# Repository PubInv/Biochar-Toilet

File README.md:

# Current Status

Phase 1 (conductive heating prototype) is complete. All experiment data, firmware, schematics, PCB design files, and progress reports are in the [`Conductive Heating Prototype/`](https://github.com/PubInv/Biochar-Toilet/tree/main/Project%20Files/Conductive%20Heating%20Prototype) folder.

We're now in Phase 2: induction heating using a magnetite matrix. The shift from resistive heating matters because induction generates heat directly inside the charring cup — no exposed coils corroding in the process environment, and faster energy delivery to the material itself.

Ongoing experiment logs are in the [Progress Reports](https://github.com/PubInv/Biochar-Toilet/blob/main/Project%20Files/Progress%20Reports.md).

---

# Biochar Toilet

A reliable toilet that could quickly reduce human fecal matter to completely sanitary biochar would make the poorest people of the
Earth healthier. In many communities, Western-style sewage systems would be very expensive and impractical due to
geology, the lack of density in farming communities made of small land holdings, a lack of capital, and a lack of
social and political organization to dig trenches and lay pipes efficiently.

Reducing a typical human stool to biochar requires an energy input of about 600 kilojoules (see detailed analysis in referenced spreadsheet).
Even for the poorest people, the cost of this electricity is quite low---less than one US cent $0.01USD. One kilowatt hour is 3.6 MJ (megajoules).
Expensive electrical power around the world is $0.45/kWh is $0.075 USD--or less than eight cents. Even if our toilet is inefficient, it
seems possible to make a toilet whose operating cost is affordable for the poorest people, at $27.375 per year (this cost does not include
the capital costs of the toilet).

Biochar can be used as a fuel or a garden amendment. Note, however, that human stools are so small (128 grams nominally) that this is not a meaningful approach for carbon sequestration.

# Initial Design Idea

The problem of toilets is a widely researched area. Our approach may be slightly novel. We start from some assumptions:

1. Electricity is an input.
2. Complete biological safety of the end product is required.
3. We choose to temporarily ignore the capital costs of the toilet in our research.
4. Because we have to char in the absence of oxygen to prevent combustion, we can assume that we need an air-tight or pressure controlled reaction vessel.
5. A major problem in charring is to first dry the sample, and drying is primarily a problem of water transport.

We therefore conclude that our basic design will be a sealed reaction vessel with a valve that allows steam to be transported out
of the reaction chamber. We will heat the chamber contents until a desired pressure is created and then transport the water
vapor away by opening the valve. The valve will be controlled so as to avoid most gases (air) from entering the chamber.
Opening the valve will "flash" the water in the sample into steam, which will have the desirable properties of being
extremely murderous to any organisms present in the sample, and physically destructive to both plant and animal cells.
It may even physically disrupt the sample, which could be advantageous.

When the sample is sufficiently dry, we will heat it to charring temperature. When the sample is fully charred, and then cooled
and possibly wetted to avoid spontaneous combustion, the operator will be alerted that the sample is safe to remove and either combust or use as a garden amendment.

# Energy Analysis

Volunteer Nupur Bhalla working with Invention Coach Robert L. Read has produced a [Google Sheet](https://docs.google.com/spreadsheets/d/1ZwIqP0B2wM6QrpZTNiK1hNnNmIEIal7qxYdgEJz8Iog/edit?usp=sharing) representing an energy analysis of the drying and heating process.

# Heating Mechanisms

Since we will have a sealed metal reaction vessel, radio frequency (RF) heating is a possibility.
However, it is expected to become less effective as the sample dries.
We therefore intend to explore the possibility of using simple Joule resistive heating of a stainless steel vessel directly.
RF heating, however, has the advantage of heating the sample volumetrically (not requiring conduction), which may be a tremendous advantage.

# Phase 1: Conductive Heating Prototype (Complete)

Phase 1 used a pressure cooker as the reaction vessel, a hot plate controlled by an SSR, and an ESP32-based sensing system. The goal was to confirm the core architecture before committing to higher-temperature methods.

It worked. When pressure drops below ~1 PSI while temperature keeps climbing, the system correctly identifies the dry state and cuts heater power automatically. Flash decompression also checked out — opening the solenoid under pressure causes trapped water to flash to steam. A bread charring test (~110°C, 2h40m) produced a visibly charred loaf, though the dryness algorithm didn't trigger since the bread's low moisture content didn't produce a distinct enough pressure signature during drying. Soot accumulation on the lid also flagged particulate management as something to design for in future iterations.

The hard limit we hit: full charring temperatures aren't safe inside a standard pressure cooker. Lawrence Kincheloe suggested placing an inner cup (heated by a silicon nitride igniter) inside the vessel so the outer shell stays cool — that idea feeds directly into Phase 2.

We also designed a custom control PCB for this phase (ESP32-H2, v0.3.0) with dual MOSFET valve drivers, dual SSR outputs, a pressure ADC, and a MAX31855 thermocouple interface. Everything is in the [`Conductive Heating Prototype/`](https://github.com/PubInv/Biochar-Toilet/tree/main/Project%20Files/Conductive%20Heating%20Prototype) folder.

# Phase 2: Induction System Development (In Progress)

We've switched from resistive heating to pulsed induction using a magnetite matrix. The magnetite sits inside the charring cup and converts the induction field directly into heat — no exposed coils, no conduction losses through the vessel wall.

Early results from Lawrence Kincheloe and Peter are encouraging. Five grams of magnetite reached 740°F in 60 seconds; the same mass of carbon steel bearings only hit 130°F. Volume-matching the steel to the magnetite closes the gap considerably (~940°F peak), which suggests surface area and density matter more than material choice at this scale. They also charred cheese puffs at 833°F over 16 minutes in open air, with residue on the crucible cap showing evidence of partial pyrolysis.

Full experiment logs are in the [Progress Reports](https://github.com/PubInv/Biochar-Toilet/blob/main/Project%20Files/Progress%20Reports.md).

# Research Plans

The next step is pushing the induction system to actual charring temperatures — hot enough to produce biochar from organic material comparable to human stool. Work on coil geometry and magnetic field focusing is ongoing in parallel with fabrication.

# References

"An Experimental 13.56 MHz Radio Frequency Heating System
for Efficient Thermal Pretreatment of Wastewater Sludge",
Md. S. Ferdous, Ehssan H. Koupaie, Cigdem Eskicioglu, and Thomas Johnson*

# Volunteer Opportunities

This project is still active. If you have a background in mechanical engineering, heat engineering, or chemistry, we'd be glad to hear from you.

Reach out to Inventor Coach [Robert L. Read](https://github.com/PubInv/Biochar-Toilet/blob/main/read.robert@gmail.com) or Volunteer Coordinator [Miriam Castillo](https://www.linkedin.com/in/cstllgtrrz/). More at the [Volunteer Page](https://www.pubinv.org/volunteer/).

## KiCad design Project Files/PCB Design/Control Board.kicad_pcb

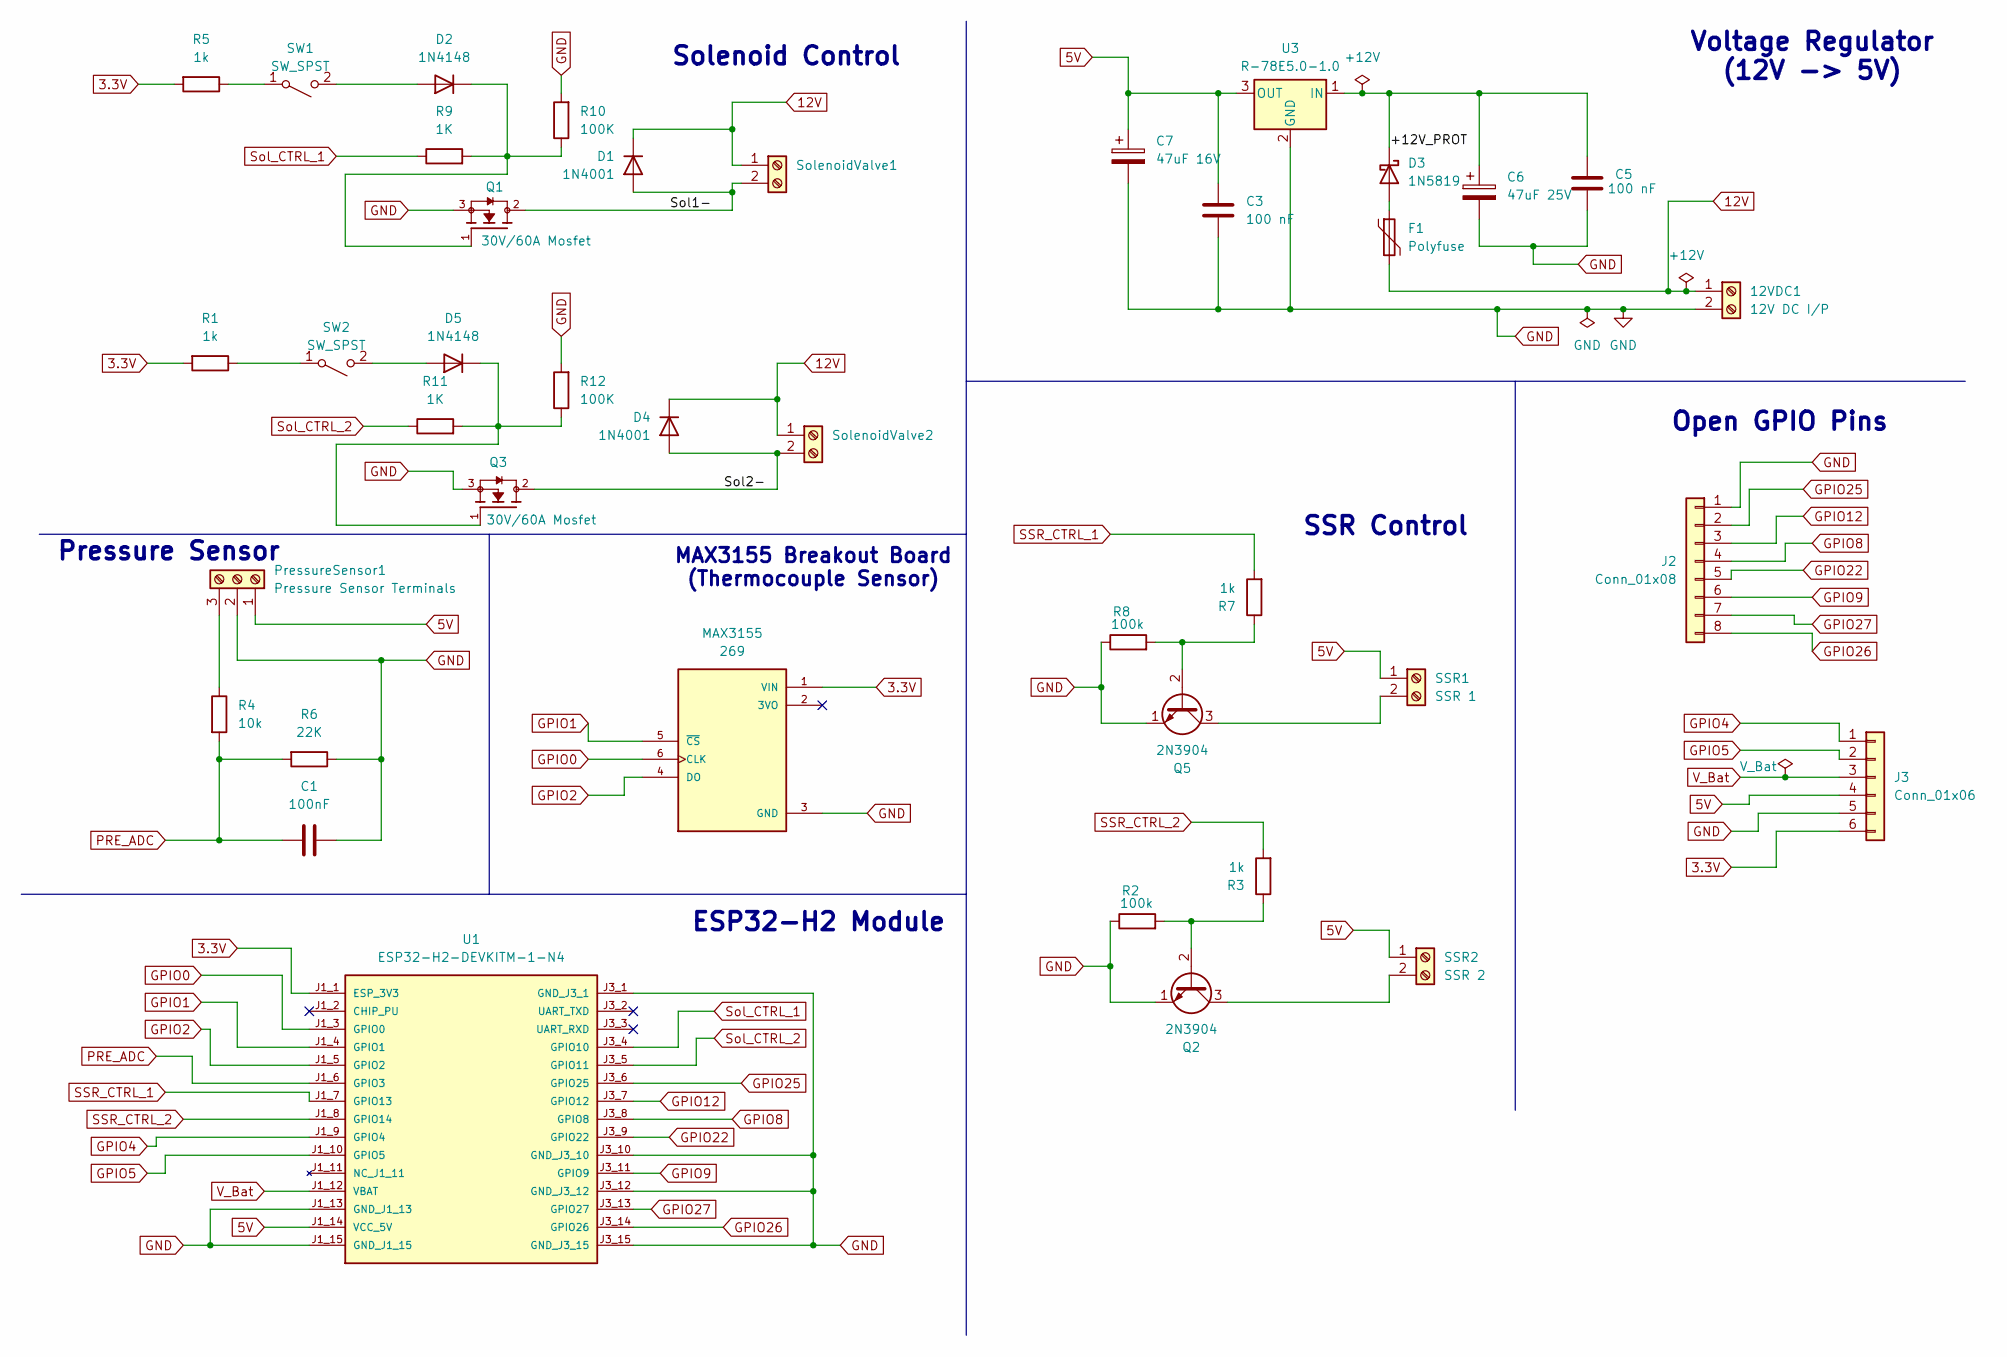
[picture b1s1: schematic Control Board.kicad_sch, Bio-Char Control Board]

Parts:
12VDC1: 12V DC I/P; TerminalBlock_Phoenix_MKDS-1,5-2-5.08_1x02_P5.08mm_Horizont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
C1: 100nF; C_Disc_D5.0mm_W2.5mm_P5.00mm
C3, C5: 100 nF; C_Disc_D5.0mm_W2.5mm_P5.00mm
C6: 47uF 25V; CP_Radial_D6.3mm_P2.50mm
C7: 47uF 16V; CP_Radial_D6.3mm_P2.50mm
D1, D4: 1N4001; D_DO-41_SOD81_P10.16mm_Horizontal
D2, D5: 1N4148; D_DO-35_SOD27_P7.62mm_Horizontal
D3: 1N5819; D_DO-41_SOD81_P10.16mm_Horizontal
F1: Polyfuse; Fuse_BelFuse_0ZRE0008FF_L8.3mm_W3.8mm
J2: Conn_01x08; PinHeader_1x08_P2.54mm_Vertical
J3: Conn_01x06; PinHeader_1x06_P2.54mm_Vertical
MAX3155: 269; MODULE_269; PARTREV 2.0
PressureSensor1: Pressure Sensor Terminals; TerminalBlock_Phoenix_MKDS-1,5-3-5.08_1x03_P5.08mm_Horizont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
Q1, Q3: 30V/60A Mosfet; TO254P1067X483X2057-3; PARTREV 4/22/09
Q2, Q5: 2N3904; TO-92_Inline
R1, R3, R5, R7: 1k; R_Axial_DIN0207_L6.3mm_D2.5mm_P7.62mm_Horizontal
R2, R8: 100k; R_Axial_DIN0207_L6.3mm_D2.5mm_P7.62mm_Horizontal
R4: 10k; R_Axial_DIN0207_L6.3mm_D2.5mm_P7.62mm_Horizontal
R6: 22K; R_Axial_DIN0207_L6.3mm_D2.5mm_P7.62mm_Horizontal
R9, R11: 1K; R_Axial_DIN0207_L6.3mm_D2.5mm_P7.62mm_Horizontal
R10, R12: 100K; R_Axial_DIN0207_L6.3mm_D2.5mm_P7.62mm_Horizontal
SSR1: SSR 1; TerminalBlock_Phoenix_MKDS-1,5-2-5.08_1x02_P5.08mm_Horizont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
SSR2: SSR 2; TerminalBlock_Phoenix_MKDS-1,5-2-5.08_1x02_P5.08mm_Horizont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
SW1, SW2: SW_SPST; PinHeader_1x02_P2.54mm_Vertical
SolenoidValve1, SolenoidValve2: TerminalBlock_Phoenix_MKDS-1,5-2-5.08_1x02_P5.08mm_Horizont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
U1: ESP32-H2-DEVKITM-1-N4; MODULE_ESP32-H2-DEVKITM-1-N4; PARTREV 1.2
U3: R-78E5.0-1.0; Converter_DCDC_RECOM_R-78E-0.5_THT

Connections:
3.3V: J3.6, MAX3155.1 (VIN), R1.2, R5.2, U1.J1_1 (ESP_3V3)
5V: C3.1, C7.1, J3.4, PressureSensor1.1, SSR1.1, SSR2.1, U1.J1_14 (VCC_5V), U3.3 (OUT)
12V: 12VDC1.1, D1.1 (K), D4.1 (K), F1.2, SolenoidValve1.1, SolenoidValve2.1
/+12V_PROT: C5.1, C6.1, D3.1 (K), U3.1 (IN)
/Sol1-: D1.2 (A), Q1.2, SolenoidValve1.2
/Sol2-: D4.2 (A), Q3.2, SolenoidValve2.2
GND: 12VDC1.2, C1.1, C3.2, C5.2, C6.2, C7.2, J2.1, J3.5, MAX3155.3 (GND), PressureSensor1.2, Q1.3, Q2.1 (E), Q3.3, Q5.1 (E), R2.1, R6.1, R8.1, R10.2, R12.2, U1.J1_13 (GND_J1_13), U1.J1_15 (GND_J1_15), U1.J3_1 (GND_J3_1), U1.J3_10 (GND_J3_10), U1.J3_12 (GND_J3_12), U1.J3_15 (GND_J3_15), U3.2 (GND)
GPIO0: MAX3155.6 (CLK), U1.J1_3 (GPIO0)
GPIO1: MAX3155.5 (~CS), U1.J1_4 (GPIO1)
GPIO2: MAX3155.4 (DO), U1.J1_5 (GPIO2)
GPIO4: J3.1, U1.J1_9 (GPIO4)
GPIO5: J3.2, U1.J1_10 (GPIO5)
GPIO8: J2.4, U1.J3_8 (GPIO8)
GPIO9: J2.6, U1.J3_11 (GPIO9)
GPIO12: J2.3, U1.J3_7 (GPIO12)
GPIO22: J2.5, U1.J3_9 (GPIO22)
GPIO25: J2.2, U1.J3_6 (GPIO25)
GPIO26: J2.8, U1.J3_14 (GPIO26)
GPIO27: J2.7, U1.J3_13 (GPIO27)
unnamed: D2.2 (A), SW1.2 (B)
unnamed: D2.1 (K), Q1.1, R9.2, R10.1
unnamed: D3.2 (A), F1.1
unnamed: D5.2 (A), SW2.2 (B)
unnamed: D5.1 (K), Q3.1, R11.2, R12.1
unnamed: PressureSensor1.3, R4.1
unnamed: Q2.2 (B), R2.2, R3.1
unnamed: Q2.3 (C), SSR2.2
unnamed: Q5.2 (B), R7.1, R8.2
unnamed: Q5.3 (C), SSR1.2
unnamed: R5.1, SW1.1 (A)
unnamed: R1.1, SW2.1 (A)
PRE_ADC: C1.2, R4.2, R6.2, U1.J1_6 (GPIO3)
SSR_CTRL_1: R7.2, U1.J1_7 (GPIO13)
SSR_CTRL_2: R3.2, U1.J1_8 (GPIO14)
Sol_CTRL_1: R9.1, U1.J3_4 (GPIO10)
Sol_CTRL_2: R11.1, U1.J3_5 (GPIO11)
V_Bat: J3.3, U1.J1_12 (VBAT)

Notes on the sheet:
SSR Control
Pressure Sensor
Voltage Regulator (12V -> 5V)
MAX3155 Breakout Board (Thermocouple Sensor)
Solenoid Control
ESP32-H2 Module
Open GPIO Pins

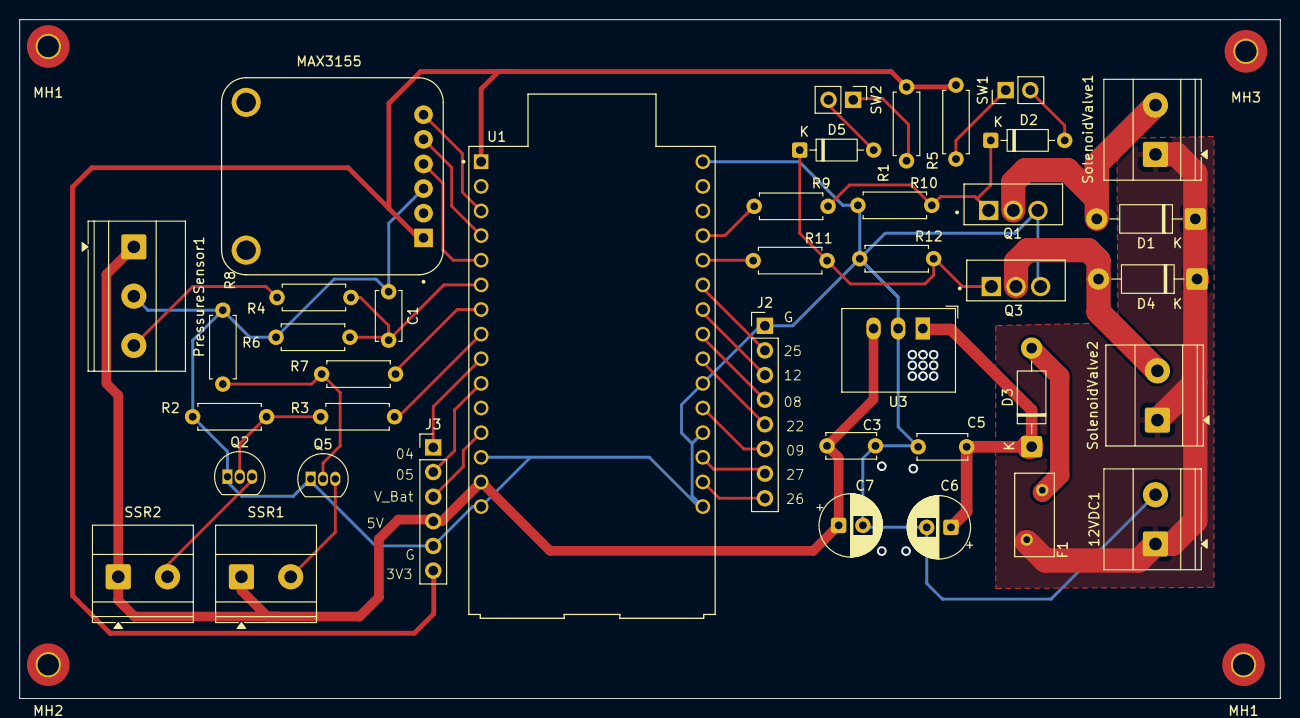
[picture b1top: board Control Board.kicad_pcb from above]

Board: 2 copper layers, 130.0 x 70.0 mm, 44 parts (0 on the bottom side), 37 nets.

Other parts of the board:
MH1, MH1#2, MH2, MH3: MountingHole_2.2mm_M2_Pad_TopBottom

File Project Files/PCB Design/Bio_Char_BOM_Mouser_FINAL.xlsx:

Bio-Char Control Board - Mouser BOM
Item | Qty | References | Value | Description | Package/Footprint | Specifications | Manufacturer | MPN | Mouser PN | Unit Price | Ext Price | Notes
▼ CAPACITORS
1 | 3 | C1, C3, C5 | 100nF | Ceramic bypass capacitors | Disc 5.0mm | 50V, X7R, ±10% | Kemet | C322C104K5R5TA7305 | 80-C322C104K5R5TA | 0.87 | 2.61 | Input/Output & MAX31855 bypass
2 | 2 | C6, C7 | 47µF 25V | Aluminum electrolytic capacitors | Radial D6.3mm P2.5mm | 25V, 105°C (C7=16V covered) | Cornell Dubilier | 476CKH025M | 598-476CKH025M | 0.21 | 0.42 | U3 input/output filtering
▼ RESISTORS (All 1/4W, Through-Hole)
3 | 6 | R1,R3,R5,R7,R9,R11 | 1kΩ | Carbon film resistors 1/4W ±5% | Axial 7.62mm | 1/4W, ±5%, 1kΩ | YAGEO | CFR-25JR-52-1K | 603-CFR-25JR-521K | 0.18 | 1.08 | Current limit, base resistors
4 | 4 | R2,R8,R10,R12 | 100kΩ | Carbon film resistors 1/4W ±5% | Axial 7.62mm | 1/4W, ±5%, 100kΩ | YAGEO | CFR-25JB-52-100K | 603-CFR-25JB-52-100K | 0.18 | 0.72 | MOSFET pull-down resistors
5 | 2 | R4, R14 | 10kΩ | Carbon film resistors 1/4W ±5% | Axial 7.62mm | 1/4W, ±5%, 10kΩ | YAGEO | CFR-25JB-52-10K | 603-CFR-25JB-52-10K | 0.1 | 0.2 | Pull-up resistors
6 | 2 | R6, R15 | 22kΩ | Carbon film resistors 1/4W ±5% | Axial 7.62mm | 1/4W, ±5%, 22kΩ | YAGEO | CFR-25JB-52-22K | 603-CFR-25JB-52-22K | 0.1 | 0.2 | Voltage divider resistors
▼ DIODES
7 | 2 | D1, D4 | 1N4001RLG | Rectifier diodes 50V 1A | DO-41 P10.16mm | 50V, 1A, DO-41 | onsemi | 1N4001RLG | 863-1N4001RLG | 0.13 | 0.26 | SSR protection diodes
8 | 2 | D2, D5 | 1N4148 | Switching diodes 100V 150mA | DO-35 P7.62mm | 100V, 150mA, DO-35 | onsemi | 1N4148 | 512-1N4148 | 0.1 | 0.2 | Flyback protection diodes
9 | 1 | D3 | 1N5819RLG | Schottky diode 40V 1A | DO-41 P10.16mm | 40V, 1A Schottky | onsemi | 1N5819RLG | 863-1N5819RLG | 0.39 | 0.39 | Reverse polarity protection
▼ MICROCONTROLLER & POWER MANAGEMENT
10 | 1 | U1 | ESP32-H2-DEVKITM-1-N4 | WiFi/BLE development module | ESP32-H2 Module | 802.11n, BLE 5.2, 4MB Flash | Espressif | ESP32-H2-DevKitM-1-N4 | 356-ESP32H2DKITM1-N4 | 9.3800000000000008 | 9.3800000000000008 | Main microcontroller
11 | 1 | U3 | R-78E5.0-1.0 | 12V→5V 1A switching regulator | SIP-3 | 8-28V in, 5V 1A out, 95% eff | RECOM | R-78E5.0-1.0 | 919-R-78E5.0-1.0 | 3.97 | 3.97 | Buck converter (no heatsink needed)
12 | 1 | F1 | Polyfuse 2A | Resettable fuse PTC 2A | Radial | 2A hold, 4A trip | Bel | 0ZRN0200FF1E | 530-0ZRN0200FF1E | 0.42 | 0.42 | Overcurrent protection
▼ POWER & SIGNAL TRANSISTORS
13 | 2 | Q1, Q3 | IRLB3813PBF | N-channel MOSFETs | TO-220 | 30V, 100A, 2.3mΩ Rds(on) | Infineon | IRLB3813PBF | 942-IRLB3813PBF | 2.16 | 4.32 | ⚠️ Upgrade from IRLB8721 - Better!
14 | 2 | Q2, Q5 | 2N3904BU | NPN transistors | TO-92 | 40V, 200mA, hFE>100 | onsemi | 2N3904BU | 512-2N3904BU | 0.28000000000000003 | 0.56000000000000005 | MOSFET gate drivers
▼ CONNECTORS & TERMINALS
15 | 5 | 12V_I/P, Sol1, Sol2, SSR1, SSR2 | Terminal 2-pos | Phoenix terminal blocks 2-position | Phoenix 5.08mm | 2-pos, 5.08mm, 90°, 12A | Phoenix Contact | 1715721 | 651-1715721 | 1.3 | 6.5 | Power input & outputs
16 | 1 | PressureSensor1 | Terminal 3-pos | Phoenix terminal block 3-position | Phoenix 5.08mm | 3-pos, 5.08mm, 90°, 12A | Phoenix Contact | 1715734 | 651-1715734 | 1.66 | 1.66 | Pressure sensor connection
17 | 2 | J2, J3 | Pin Headers | Pin headers 2.54mm | 2.54mm vertical | 1x8 + 1x6, single row | Amphenol ICC | 10129379-908001BLF | 649-1012937990801BLF | 0.14000000000000001 | 0.28000000000000003 | I/O & MAX31855 connectors
▼ BREAKOUT MODULES
18 | 1 | MAX3155 | MAX31855 | Thermocouple amplifier breakout | Adafruit #269 | K-type, -200°C to +700°C, SPI | Adafruit | 269 | 485-269 | 14.95 | 14.95 | Thermocouple interface module
TOTAL COST: |  |  |  |  |  |  |  |  |  | 48.120000000000005 | 48.120000000000005

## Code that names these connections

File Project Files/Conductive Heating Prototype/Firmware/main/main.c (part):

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 * SDK:     ESP-IDF v5.x
 *
 * Pin Configuration (corrected from PCB schematic — see notes below):
 *   GPIO0  → MAX31855 CLK
 *   GPIO1  → MAX31855 CS
 *   GPIO2  → MAX31855 DO (MISO — read-only, no MOSI needed)
 *   GPIO3  → Pressure Sensor ADC  (ADC1_CH2, 0–100 PSI via voltage divider)
 *   GPIO4  → SSR 1 / Heater       (active HIGH — drives BJT base to complete SSR circuit)
 *   GPIO5  → SSR 2                (reserved, not currently active — see commented code)
 *   GPIO8  → WS2812 RGB LED       (Status Indicator)
 *   GPIO10 → Solenoid Valve 1     (MOSFET-driven)
 *   GPIO11 → Solenoid Valve 2     (reserved, not currently active — see commented code)
 *   GPIO12 → Flush Button         (Active LOW with internal pull-up)
 *
 * PIN CONFIGURATION NOTES:
 *   GPIO14 and GPIO15 are reserved for 32 kHz RTC crystal on some variants.
 *   GPIO3 is shared with MTDI/JTAG.
 *
 * HEATER/SSR CHANGE vs ARDUINO VERSION:
 *   The Arduino version used active LOW (GPIO4 LOW = SSR ON, sinking to GND).
 *   This board uses a BJT (NPN) between the ESP32 GPIO and the SSR input:
 *     GPIO4 HIGH → BJT base HIGH → collector pulls SSR input LOW → SSR ON
 *     GPIO4 LOW  → BJT OFF → SSR input floating/HIGH → SSR OFF
 *   set_heater() has been updated accordingly.
 *
 * KNOWN ERRORS / ISSUES:
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 *   2. MAX31855 returns NAN on first read after power-on (~100ms settling time).
 *      The EMA initialisation handles this gracefully — temp_ema stays NAN until
 *      a valid reading arrives.
 *   3. GPIO3 on ESP32-H2 is shared with the JTAG interface (MTDI). Disconnect
 *      the JTAG debugger before running in production, or remap to GPIO4/5 if
 *      debugging under load is required.
 */

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// ===============================================================
// -------------------------- PINS --------------------------------
// ===============================================================
#define PIN_ADC_PRESSURE  ADC_CHANNEL_2   // GPIO3 — Pressure sensor (ADC1_CH2)
#define PIN_VALVE         GPIO_NUM_10     // GPIO10 — Solenoid Valve 1 (MOSFET)
#define PIN_HEATER        GPIO_NUM_4      // GPIO4 — SSR 1 (active HIGH → BJT → SSR)
#define PIN_LED_WS2812    GPIO_NUM_8      // GPIO8  — Onboard WS2812 RGB Status LED
#define PIN_FLUSH_BUTTON  GPIO_NUM_12     // GPIO12 — Manual Flush Button (Active LOW with internal pull-up)

// Reserved for future use — uncomment when second SSR and valve are needed
// #define PIN_SSR2    GPIO_NUM_5    // GPIO5  — SSR 2 circuit (not currently active)
// #define PIN_VALVE2  GPIO_NUM_11   // GPIO11 — Solenoid Valve 2 (not currently active)

// ===============================================================
// ------------------- PRESSURE CALIBRATION ----------------------
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}

static void set_heater(bool on) {
    // Active HIGH: GPIO4 HIGH → BJT base HIGH → collector completes SSR circuit → SSR ON
    // Active LOW (off):  GPIO4 LOW  → BJT OFF → SSR OFF
    gpio_set_level(PIN_HEATER, (on && !emergency_tripped && current_state == STATE_HEATING) ? 1 : 0);
}

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    ESP_LOGI(TAG, "║   - Dry Boiler Protection                      ║");
    ESP_LOGI(TAG, "╚════════════════════════════════════════════════╝");
    ESP_LOGI(TAG, "Pin map:");
    ESP_LOGI(TAG, "  GPIO0  → MAX31855 CLK");
    ESP_LOGI(TAG, "  GPIO1  → MAX31855 CS");
    ESP_LOGI(TAG, "  GPIO2  → MAX31855 DO");
    ESP_LOGI(TAG, "  GPIO3  → Pressure Sensor ADC");
    ESP_LOGI(TAG, "  GPIO4  → SSR 1 (active HIGH, BJT driver)");
    ESP_LOGI(TAG, "  GPIO5  → SSR 2 (reserved)");
    ESP_LOGI(TAG, "  GPIO8  → WS2812 RGB LED Status Indicator");
    ESP_LOGI(TAG, "  GPIO10 → Solenoid Valve 1");
    ESP_LOGI(TAG, "  GPIO11 → Solenoid Valve 2 (reserved)");
    ESP_LOGI(TAG, "  GPIO12 → Flush Button (Active LOW)");

    window_start = esp_timer_get_time() / 1000LL;
    valve_window_start = window_start;
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
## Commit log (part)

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2025-06-22 initial commit of LICENSE and README
2025-06-22 improving README
2025-10-08 Update README.md
    @RobertLRead @castleyeo
    I added a volunteer request section to the bottom of this project's README since it is still active. Let me know if you have any corrections, and I will also add a project page for it on WordPress.
2025-10-10 Document Flash System Prototype test cases
    Added initial test cases for Flash System Prototype, including solenoid control and temperature sensing.
2026-02-13 Update project status: SSR control integration, and initial charring test results
    - Resealed chamber valves to resolve pressure leaks
    - Recalibrated pressure sensor against manual gauge
    - Integrated SSR-based hotplate control
    - Validated dryness detection logic under low-pressure conditions
    - Conducted initial bread charring experiment (~110C, 2h40m)
    - Observed soot deposition inside chamber
2026-02-13 Create Control Board
2026-02-13 Add KiCad version information to Control Board.md
2026-02-19 Control Board Schematics
    - Updated the Schematics for better understanding
2026-03-15 docs: add comprehensive project review in REVIEW.md
    Add `REVIEW.md` containing a project summary, code review identifying bugs
    in the python controllers, a design review covering mechanical and safety
    concerns, and a list of recommended next steps based on the codebase analysis.
2026-03-18 Add files via upload
    Update schematic to v0.3.0
    - Updated component values
    - Verified all connections
    - Ready for PCB layout
2026-03-18 Add files via upload
    Add verified Mouser BOM with complete pricing
    - 18 component types, 40 total items
    - Total cost: $48.12 (verified March 2026)
    - All Mouser part numbers verified
    - Automatic pricing formulas included
    - Ready to order directly from Mouser
2026-03-18 Add files via upload
    Add manufacturing Gerber files
    - Complete gerber set for PCB fabrication
    - Top and bottom copper layers
    - Soldermask and silkscreen layers
    - Edge cuts and board outline
    - Ready to send to manufacturer
2026-03-18 Add files via upload
    Add drill files for PCB manufacturing
    - NC drill files for through-holes and vias
    - Compatible with standard CNC drilling equipment
2026-03-20 Update BOM with requested items
    - Added Camera Pole Mount Bracket from Amazon
    - Added Fuel Cell Bulkhead Adapter Fittings from Summit Racing
    - Added three PTFE-related components from McMaster-Carr
    - Added MEAN WELL RSP-2400 power supply
2026-03-20 Add 8 more new items to the BOM file
2026-03-20 Fix column headers and alignment in BOM
2026-03-20 Update progress report with recent project developments
    Added detailed progress updates on project BOM and testing results.
2026-03-20 Update progress report with new material specifications
    Added details about materials and components for the induction coil system.
2026-03-23 docs(BOM): Add an 'Acquired' checklist column
    - Added a new `Acquired` column to the Markdown table in `Project Files/BOM/1st_Action_Pyrolysis_BOM.md` to track item procurement.
    - Initialized all rows with a `[ ]` check mark box.
2026-03-26 Update TODO.md with areas for testing and benchmarking improvement
2026-03-27 Update progress report with new experiment details
    Added progress report for experiment on cheese puffs.
2026-03-27 Revise cheese puff experiment report
    Updated experiment report with corrected details and results.
2026-03-27 Add README for Media directory
2026-03-31 Mark items as acquired in BOM
    Updated the status of several items to 'acquired' and marked them accordingly.
2026-04-25 Fix formatting and clarify entries in experimental data
    Updated data table for induction experiments to correct formatting and clarify entries.
2026-04-25 Rename Progress Reports to Progress Reports.md
2026-05-19 Add Biochar Toilet presentation slide deck
    Created a new Presentations directory and added an HTML slide deck
    outlining the Biochar Toilet project, its mission, and the technical
    architecture (including the induction innovations and magnetite matrix).
2026-05-19 Add four new deep dive slides to the presentation.
    Added informational slides with pros and cons for Traditional Sewage,
    Composting Toilets, Incinerating Toilets, and the Biochar Toilet. Added
    hyperlinks to external resources for the facts presented on each slide.
2026-05-20 Document valorization system in DESIGN_IDEAS.md
    Added a section to `DESIGN_IDEAS.md` documenting the usage of a
    modified pressure cooker with a 1" solenoid, large induction heating
    loop, and the role of the pressure sensor in monitoring valorization.
2026-05-20 Add "Why Not Sewage" and "Why Pyrolysis Over Incineration" slides
    - Extracted two additional slides from the provided mockup and integrated them into `Presentations/Biochar_Toilet_Slide_Deck.html`.
    - Inserted "Beyond the Flush: Why Not Sewage?" immediately after the traditional sewage deep dive.
    - Inserted "Why Pyrolysis Over Incineration?" immediately after the incinerating toilets deep dive.
    - Renumbered slide comments to maintain the correct sequential order (now up to 16 slides).
2026-05-20 Update presenter names in slide deck
2026-05-20 Correct spelling of 'Robert Reed' to 'Robert Read'
2026-05-20 Fix text legibility on "Open Source Collaboration" slide
    - Applies inline CSS `color: #e2e8f0` to the list items on Slide 15 so they contrast properly with the dark background.
2026-05-21 feat: implement interactive presentation mode with fullscreen support
    Added a "Present" button to the bottom right of `Biochar_Toilet_Slide_Deck.html` that toggles a fullscreen presentation mode.
    Implemented JavaScript logic to hook into the Fullscreen API, dynamically scale active `.slide-container` elements to fit the viewport, hide inactive slides, and handle navigation via `ArrowRight` an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
2026-05-21 Add script to convert images to WebP format
    Added `Presentations/convert_to_webp.py` that takes a folder path as an argument and iterates through standard image formats, converting them to `.webp` format using `cwebp` at a quality setting of 8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
2026-05-21 Update presentation deck with images\n\n- Add images to the water scarcity slide\n- Add images to the hardware layout slide\n- Ensure proper formatting for responsive rendering of images
2026-05-22 Update presentation: move logo to slide 1 and increase size to 250px
    This commit moves the original image from slide 2 to the title slide
    acting as a project logo and increases its size to 250px as requested.
    The new architectural diagram is displayed on slide 2 with `object-fit: contain`.
2026-05-22 Update presentation: remove border radius from slide 1 logo
    This commit removes the `border-radius: 50%` style from the logo image
    on slide 1 to prevent its corners from being cut off.
2026-05-22 Add Conductive Heating Prototype video to presentation
    - Downloaded the conductive heating prototype video.
    - Embedded the video in a new slide in `Presentations/Biochar_Toilet_Slide_Deck.html` after Slide 14.
    - Verified visual presentation with Playwright.
2026-05-22 feat(presentation): add Phase 1 Control Board slide
2026-05-25 Revise project status and details in README
    Updated the README to reflect the current status of the Biochar Toilet project, including progress on Phase 1 and Phase 2, and revised descriptions for clarity.
2026-05-25 docs: consolidate comparison slides and add concrete stats
    - Consolidated slides 6-9 into a single "Why Pyrolysis Over Alternatives?" slide focusing on safety, convenience, energy efficiency, and rapid heating.
    - Updated "The Infrastructure Gap" slide with concrete 2025 WHO/UNICEF statistics.
    - Added tasks to TODO.md to capture the team's story and write a snappy script for the presentation.
2026-05-26 Fix grammar in Progress Reports.md
2026-05-26 Add Phase 1 documentation for Biochar Toilet project
    Added Phase 1 documentation for the Biochar Toilet project, detailing system architecture, hardware components, firmware, known issues, experiment timeline, and conclusions.
2026-05-26 Add CMakeLists.txt for biochar_control project
2026-06-07 Add script to export presentation deck for offline mode
    Added a new Python script `export_offline.py` that processes the existing
    `Biochar_Toilet_Slide_Deck.html` and downloads external assets (fonts, images,
    videos, scripts), base64 encodes them, and inlines them to generate a fully
    standalone offline presentation deck `Biochar_Toilet_Slide_Deck_Offline.html`.
    The generated HTML file is explicitly added to `.gitignore` to avoid committing
    large build artifacts.
2026-06-09 Add induction coil overview slide to presentation
2026-06-10 Make convert_to_webp.py cross-platform with OS-specific instructions
    - Use platform.system() to dynamically locate the cwebp binary
    - Search for libwebp-1.6.0-windows-x64 locally and via PATH for Windows
    - Fall back to PATH for macOS and Linux
    - Provide OS-specific installation instructions when cwebp is not found
2026-06-10 Add bash script to build firmware for ESP32-H2
2026-06-10 Add firmware build scripts for ESP32-H2 (Windows and Linux/macOS)
2026-06-10 Ensure ESP-IDF toolchain is installed unconditionally
2026-06-11 feat: expand engineering facts on Buffer & Batch slide
    Updated the 'The "Buffer & Batch" Architecture' slide in Biochar_Toilet_Slide_Deck.html to include more specific technical details such as tank capacities, NEMA stepper motor torque specs, active dos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
    Adjusted the inline styling of the tile grid layout and inner lists to ensure the expanded facts comfortably fit within the UI while strictly preserving the overall presentation CSS theme.
2026-06-11 feat: mark specific slides as Future Goals
    Updated the slide titles for "The 'Buffer & Batch' Architecture" and "Secondary Catalytic Filtration: Zero Emissions" to append "(Future Goal)" per user feedback, clarifying project roadmap status in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
2026-06-11 Ensure ESP-IDF toolchain is installed unconditionally and ESP-IDF v6 compiles
2026-06-11 Update induction hardware slides in presentation deck
    - Replaced obsolete 'Potted Internal Coil' slide with updated 'Induction Hardware: Current Development Status'.
    - Added new 'From Kitchenware to Prototype' slide detailing the fabrication process and accessibility principles.
    - Updated FontAwesome icon to a free variant (`fa-kitchen-set`) for correct rendering.
    - Removed extraneous markdown backticks from the source content.
2026-06-11 Fix mobile responsiveness in HTML presentation deck
2026-06-13 Fix CMake build by using driver component instead of standalone gpio/spi drivers
    This updates the `CMakeLists.txt` for the ESP32-H2 firmware so that it uses the umbrella `driver` component rather than `esp_driver_gpio` and `esp_driver_spi`. In ESP-IDF v5.2, these specific drivers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
2026-06-13 Fix ESP-IDF firmware build scripts failing on `fullclean`
    Added explicit cleanup of the `build` directory (`rm -rf build` and `if exist build rmdir /s /q build`) to the `.sh` and `.bat` firmware build scripts. This prevents `idf.py fullclean` from failing a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
2026-06-15 ⚡ Bolt: Optimize slide deck media loading with lazy and preload attributes
2026-06-16 🎨 Palette: Fix keyboard navigation focus bug in presentation mode
2026-06-17 ⚡ Bolt: cache redundant network requests in export_offline.py
    💡 What: Implemented dictionary-based `url_cache` and `file_cache` in `Presentations/export_offline.py` for remote and local assets.
    🎯 Why: The export script repeatedly fetched the same CSS and font files over the network (e.g. `requests.get`) because the presentation references them multiple times.
    📊 Impact: Reduces offline HTML generation time from ~3.7 seconds to ~2.8 seconds, eliminating ~15 redundant network requests and saving bandwidth.
    🔬 Measurement: Compare `time python export_offline.py` before and after.
